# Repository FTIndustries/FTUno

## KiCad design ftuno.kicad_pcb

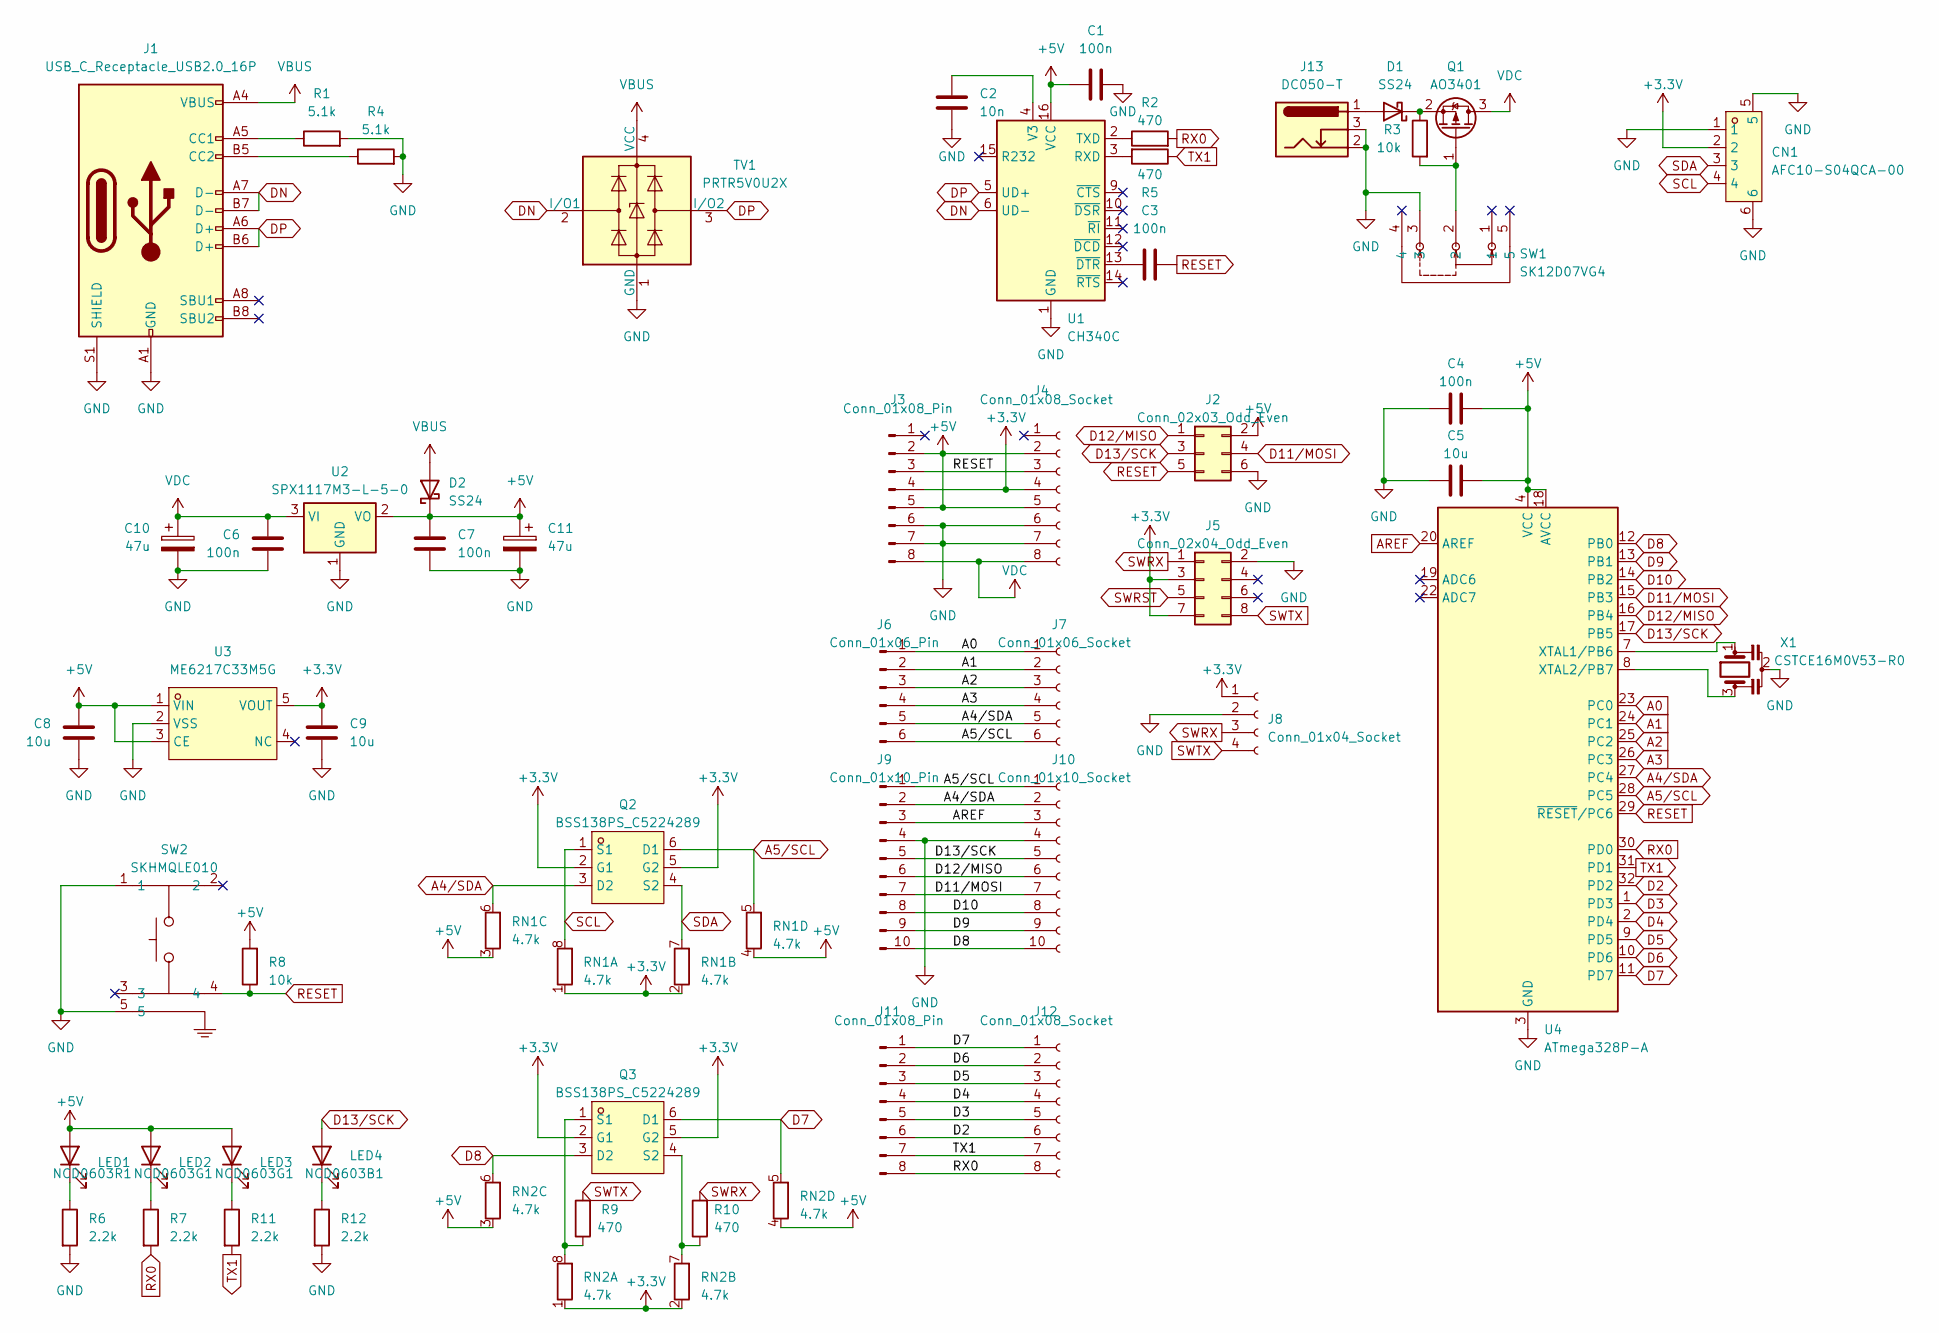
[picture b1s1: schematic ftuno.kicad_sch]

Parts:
C1, C3, C6, C7: 100n; C_0603_1608Metric
C2: 10n; C_0402_1005Metric
C4: 100n; C_0402_1005Metric
C5, C8, C9: 10u; C_0603_1608Metric
C10, C11: 47u; CP_Elec_6.3x5.4; LCSC Part C2836440
CN1: AFC10-S04QCA-00; CONN-SMD_AFC10-S04QCA-00; LCSC Part C2764183
D1, D2: SS24; D_SMA
J1: USB_C_Receptacle_USB2.0_16P; USB_C_Receptacle_G-Switch_GT-USB-7010ASV
J2: Conn_02x03_Odd_Even; PinHeader_2x03_P2.54mm_Vertical
J3, J11: Conn_01x08_Pin; PinHeader_1x08_P2.54mm_Vertical
J4, J12: Conn_01x08_Socket; PinSocket_1x08_P2.54mm_Vertical
J5: Conn_02x04_Odd_Even; PinSocket_2x04_P2.54mm_Vertical
J6: Conn_01x06_Pin; PinHeader_1x06_P2.54mm_Vertical
J7: Conn_01x06_Socket; PinSocket_1x06_P2.54mm_Vertical
J8: Conn_01x04_Socket; PinSocket_1x04_P2.54mm_Vertical
J9: Conn_01x10_Pin; PinHeader_1x10_P2.54mm_Vertical
J10: Conn_01x10_Socket; PinSocket_1x10_P2.54mm_Vertical
J13: DC050-T; DC-IN_DC050-T; LCSC Part C431534
LED1: NCD0603R1; LED_0603_1608Metric
LED2, LED3: NCD0603G1; LED_0603_1608Metric
LED4: NCD0603B1; LED_0603_1608Metric
Q1: AO3401; SOT-23
Q2, Q3: BSS138PS_C5224289; SOT-363_L2.1-W1.3-P0.65-LS2.3-BL; LCSC Part C5224289
R1, R4: 5.1k; R_0402_1005Metric
R2, R5, R9, R10: 470; R_0402_1005Metric
R3: 10k; R_0603_1608Metric
R6, R7, R11, R12: 2.2k; R_0402_1005Metric
R8: 10k; R_0402_1005Metric
RN1, RN2: 4.7k; R_Array_Convex_4x0603
SW1: SK12D07VG4; SW-TH_SK12D07VG4; LCSC Part C393937
SW2: SKHMQLE010; KEY-SMD_4P-L6.2-W6.5-P4.50-LS8.0_SKHMXX; LCSC Part C139767
TV1: PRTR5V0U2X; SOT-143
U1: CH340C; SOIC-16_3.9x9.9mm_P1.27mm
U2: SPX1117M3-L-5-0; SOT-223-3_TabPin2
U3: ME6217C33M5G; SOT-23-5_L3.0-W1.7-P0.95-LS2.8-BR; LCSC Part C427602
U4: ATmega328P-A; TQFP-32_7x7mm_P0.8mm
X1: CSTCE16M0V53-R0; OSC-SMD_3P-L3.2-W1.3-P0.95-L; LCSC Part C32180

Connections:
+3.3V: C9.1, CN1.2, J3.4, J4.4, J5.3, J5.7, J8.1, Q2.2 (G1), Q2.5 (G2), Q3.2 (G1), Q3.5 (G2), RN1.1 (R1.1), RN1.2 (R2.1), RN2.1 (R1.1), RN2.2 (R2.1), U3.5 (VOUT)
+5V: C1.1, C4.2, C5.2, C7.1, C8.1, C11.1, D2.1 (K), J2.2, J3.2, J3.5, J4.2, J4.5, LED1.2 (A), LED2.2 (A), LED3.2 (A), R8.2, RN1.3 (R3.1), RN1.4 (R4.1), RN2.3 (R3.1), RN2.4 (R4.1), U1.16 (VCC), U2.2 (VO), U3.1 (VIN), U3.3 (CE), U4.4 (VCC), U4.6 (VCC), U4.18 (AVCC)
A0: J6.1, J7.1, U4.23 (PC0)
A1: J6.2, J7.2, U4.24 (PC1)
A2: J6.3, J7.3, U4.25 (PC2)
A3: J6.4, J7.4, U4.26 (PC3)
A4/SDA: J6.5, J7.5, J9.2, J10.2, Q2.3 (D2), RN1.6 (R3.2), U4.27 (PC4)
A5/SCL: J6.6, J7.6, J9.1, J10.1, Q2.6 (D1), RN1.5 (R4.2), U4.28 (PC5)
AREF: J9.3, J10.3, U4.20 (AREF)
D2: J11.6, J12.6, U4.32 (PD2)
D3: J11.5, J12.5, U4.1 (PD3)
D4: J11.4, J12.4, U4.2 (PD4)
D5: J11.3, J12.3, U4.9 (PD5)
D6: J11.2, J12.2, U4.10 (PD6)
D7: J11.1, J12.1, Q3.6 (D1), RN2.5 (R4.2), U4.11 (PD7)
D8: J9.10, J10.10, Q3.3 (D2), RN2.6 (R3.2), U4.12 (PB0)
D9: J9.9, J10.9, U4.13 (PB1)
D10: J9.8, J10.8, U4.14 (PB2)
D11/MOSI: J2.4, J9.7, J10.7, U4.15 (PB3)
D12/MISO: J2.1, J9.6, J10.6, U4.16 (PB4)
D13/SCK: J2.3, J9.5, J10.5, LED4.2 (A), U4.17 (PB5)
DN: J1.A7 (D-), J1.B7 (D-), TV1.2 (I/O1), U1.6 (UD-)
DP: J1.A6 (D+), J1.B6 (D+), TV1.3 (I/O2), U1.5 (UD+)
GND: C1.2, C2.2, C4.1, C5.1, C6.2, C7.2, C8.2, C9.2, C10.2, C11.2, CN1.1, CN1.5, CN1.6, J1.A1 (GND), J1.A12 (GND), J1.B1 (GND), J1.B12 (GND), J1.S1 (SHIELD), J2.6, J3.6, J3.7, J4.6, J4.7, J5.2, J8.2, J9.4, J10.4, J13.2, J13.3, R1.2, R4.2, R6.2, R12.2, SW1.3, SW2.1, SW2.5, TV1.1 (GND), U1.1 (GND), U2.1 (GND), U3.2 (VSS), U4.3 (GND), U4.5 (GND), U4.21 (GND), X1.2
unnamed: D1.2 (A), J13.1
unnamed: D1.1 (K), Q1.2 (S), R3.1
unnamed: J1.A5 (CC1), R1.1
unnamed: J1.B5 (CC2), R4.1
unnamed: LED1.1 (K), R6.1
unnamed: LED2.1 (K), R7.1
unnamed: LED3.1 (K), R11.1
unnamed: LED4.1 (K), R12.1
unnamed: Q1.1 (G), R3.2, SW1.2
unnamed: Q3.1 (S1), R9.1, RN2.8 (R1.2)
unnamed: Q3.4 (S2), R10.1, RN2.7 (R2.2)
unnamed: R5.2, U1.3 (RXD)
unnamed: R2.1, U1.2 (TXD)
unnamed: C2.1, U1.4 (V3)
unnamed: C3.1, U1.13 (~DTR)
unnamed: U4.7 (XTAL1/PB6), X1.1
unnamed: U4.8 (XTAL2/PB7), X1.3
RESET: C3.2, J2.5, J3.3, J4.3, R8.1, SW2.4, U4.29 (~RESET/PC6)
RX0: J11.8, J12.8, R2.2, R7.2, U4.30 (PD0)
SCL: CN1.4, Q2.1 (S1), RN1.8 (R1.2)
SDA: CN1.3, Q2.4 (S2), RN1.7 (R2.2)
SWRST: J5.5
SWRX: J5.1, J8.3, R10.2
SWTX: J5.8, J8.4, R9.2
TX1: J11.7, J12.7, R5.1, R11.2, U4.31 (PD1)
VBUS: D2.2 (A), J1.A4 (VBUS), J1.A9 (VBUS), J1.B4 (VBUS), J1.B9 (VBUS), TV1.4 (VCC)
VDC: C6.1, C10.1, J3.8, J4.8, Q1.3 (D), U2.3 (VI)

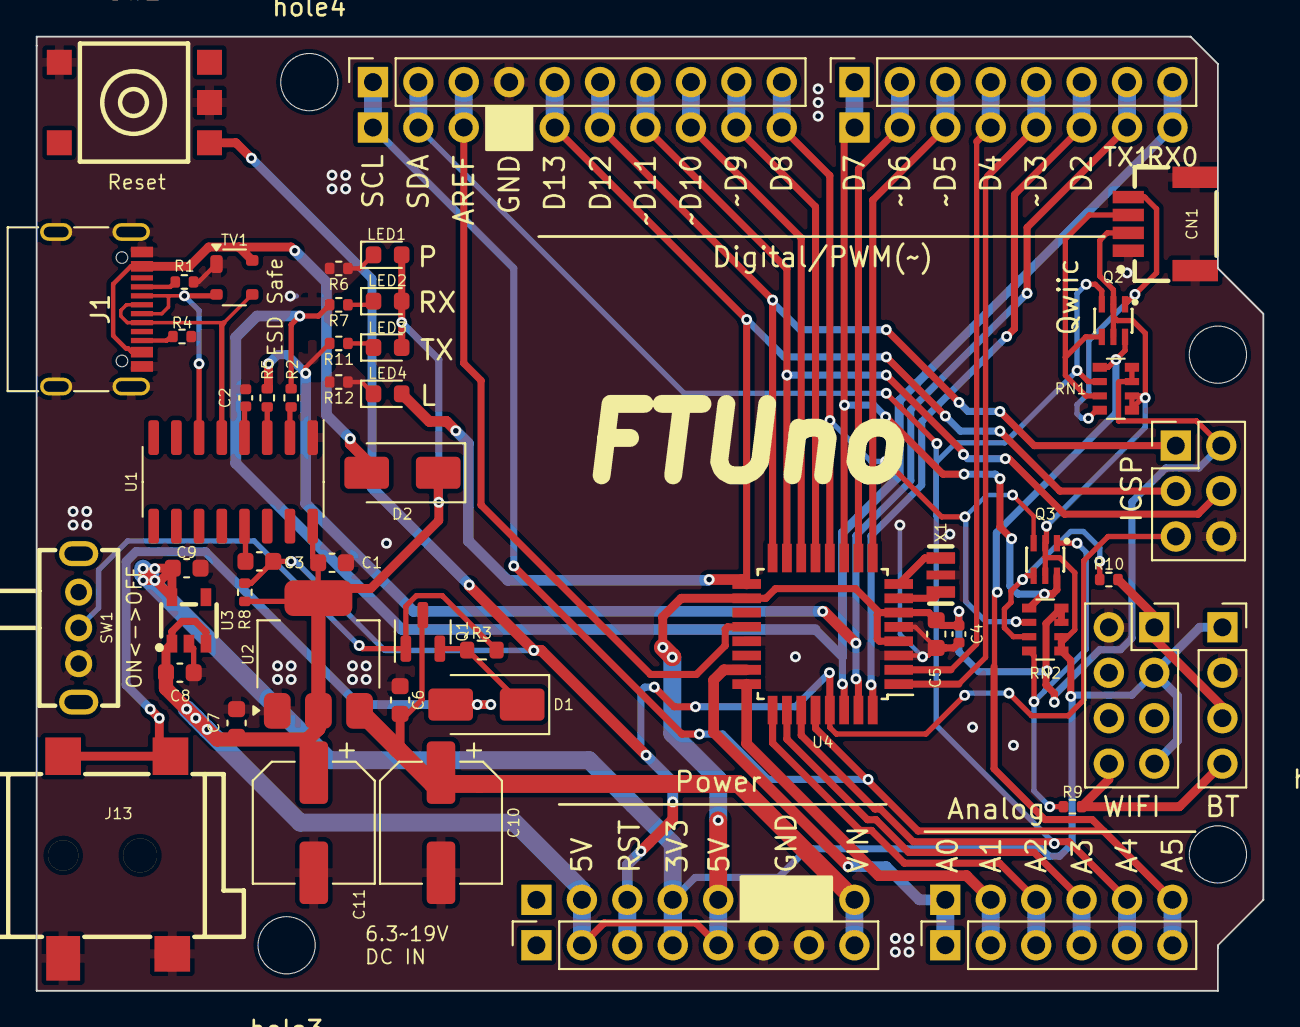
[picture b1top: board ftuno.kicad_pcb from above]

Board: 2 copper layers, 68.6 x 53.3 mm, 60 parts (0 on the bottom side), 50 nets.

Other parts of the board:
hole1, hole2, hole3, hole4: MountingHole_3.2mm_M3

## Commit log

2024-01-03 adsf
2024-01-03 added UART level convertor, moved components, solved UART LED issue
2024-01-06 change softwareserial pin to D7, D8
2024-01-10 smaller reference text
2024-01-29 use more common DC conn
2024-04-21 fix qwiic
2024-04-23 PCB update, replace USB conn, replace TVS, cleanup
2024-05-10 gitignore
2024-05-19 get rid of buck convertor and use LDO instead
2024-05-29 fix qwiic pin arrangement, move usb conn
2024-09-02 refine 1117 in and out
2024-11-29 silkscreen rework
2024-12-11 use seperate resistors for led, use higher rns for level shifters
